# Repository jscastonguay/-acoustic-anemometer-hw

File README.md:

# Acoustic Anemometer - HW
An acoustic anemometer. This is the HW part of the project.

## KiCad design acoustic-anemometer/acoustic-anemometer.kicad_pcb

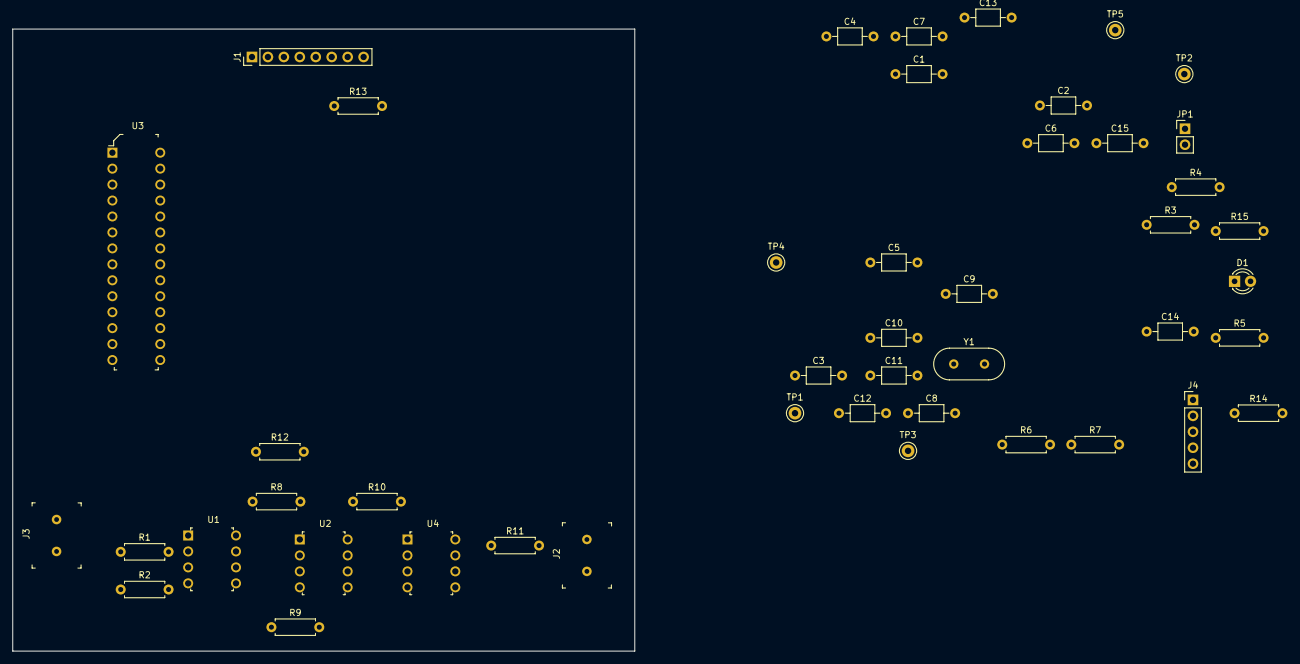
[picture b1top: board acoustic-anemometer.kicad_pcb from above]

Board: 2 copper layers, 99.1 x 99.1 mm, 46 parts (0 on the bottom side), 32 nets, no tracks yet.

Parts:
C1, C2, C4, C5, C7: 0.1u; C_Axial_L3.8mm_D2.6mm_P7.50mm_Horizontal
C3, C6, C8, C9, C12, C13, C15: 100u; C_Axial_L3.8mm_D2.6mm_P7.50mm_Horizontal
C10, C11: C; C_Axial_L3.8mm_D2.6mm_P7.50mm_Horizontal
C14: 10u; C_Axial_L3.8mm_D2.6mm_P7.50mm_Horizontal
D1: LED; LED_D3.0mm
J1: Conn_01x08; Pin_Header_Straight_1x08_Pitch2.54mm
J2, J3: OSTTC022162; Term_Block_1x2_P5.08MM
J4: Conn_01x05; Pin_Header_Straight_1x05_Pitch2.54mm
JP1: Jumper; Pin_Header_Straight_1x02_Pitch2.54mm
R1, R2, R3, R4, R5, R6, R7, R8, R9, R10, R11, R12, R13: 10k; R_Axial_DIN0207_L6.3mm_D2.5mm_P7.62mm_Horizontal
R14: 5k; R_Axial_DIN0207_L6.3mm_D2.5mm_P7.62mm_Horizontal
R15: R; R_Axial_DIN0207_L6.3mm_D2.5mm_P7.62mm_Horizontal
TP1, TP2, TP3, TP4, TP5: TestPoint; Test_Point_D1.02mm
U1, U2, U4: MCP6S21; DIP-8_W7.62mm
U3: DSPIC33EV256GM002_I_SP; DIP-28_W7.62mm
Y1: Crystal; Crystal_HC18-U_Vertical

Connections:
+5V: C1.1, C2.1, C4.1, C5.1, C7.1, J1.1, J4.2, R1.1, R3.1, R8.1, R10.1, R12.1, R14.1, U1.8, U2.8, U3.13, U3.28, U4.8
/C1IN1+: JP1.2, R3.2, R4.1, U3.6
/C1IN1-: C15.1, J1.7, R12.2, R13.1, TP5.1, U3.4, U3.5, U3.7, U3.18
/C2IN1+: R4.2, R5.1, U3.3
/C4IN1+: R5.2, R6.1, U3.16
/C5IN1+: R6.2, R7.1, U3.12
/CVREF1O: JP1.1, U3.17
/LED: R15.1, U3.26
/OSC1: C10.1, U3.9, Y1.1
/OSC2: C11.1, U3.10, Y1.2
/PGEC2: J4.5, U3.15
/PGED2: J4.4, U3.14
/SCK2: J1.6, U1.7, U2.7, U3.22, U4.7
/SDO2: J1.5, U1.6, U2.6, U3.21, U4.6
/SIGNAL_TX: J3.1, U3.25
/U1RX: J1.2, U3.24
/U1TX: J1.3, U3.11
/~MCLR: J4.1, R14.2, U3.1
/~SS2: J1.4, U1.5, U2.5, U3.23, U4.5
GND: C1.2, C2.2, C4.2, C5.2, C6.2, C7.2, C9.2, C10.2, C11.2, C13.2, C14.2, D1.1, J1.8, J2.2, J3.2, J4.3, R2.2, R7.2, R9.2, R11.2, R13.2, TP2.1, U1.4, U2.4, U3.8, U3.19, U3.27, U4.4
unnamed: C3.1, R1.2, R2.1, TP1.1, U1.2
unnamed: C3.2, J2.1
unnamed: C6.1, U1.3
unnamed: C8.1, R8.2, R9.1, TP3.1, U2.2
unnamed: C8.2, U1.1
unnamed: C9.1, U2.3
unnamed: C12.1, R10.2, R11.1, TP4.1, U4.2
unnamed: C12.2, U2.1
unnamed: C13.1, U4.3
unnamed: C14.1, U3.20
unnamed: C15.2, U4.1
unnamed: D1.2, R15.2

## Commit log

2019-05-09 During dev.
